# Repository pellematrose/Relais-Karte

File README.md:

# Relais-Karte

Relais-Karte für 24V-Systeme, zum schalten von induktiven Lasten.

---

## 🔧 Gedachte Verwendung

Über **J1** wird die Schaltung mit Strom versorgt.  
Über **J2** kann eine weitere Platine mit Spannung versorgt werden.

Eine **Autosicherung** schützt die Schaltung bzw. die angeschlossene Last.

Der **Schiebeschalter** ermöglicht es, die Last **unabhängig vom Relais** einzuschalten.

---

## 💡 Statusanzeigen (LEDs)

Die Platine verfügt über **zwei LEDs zur Zustandsanzeige**:

- **LED 1 – Versorgung & Sicherung OK**  
  - Leuchtet, wenn **Spannung anliegt** und die **Sicherung in Ordnung** ist

- **LED 2 – Relais aktiv / Last versorgt**  
  - Leuchtet, wenn das **Relais geschaltet hat** oder der **manuelle Schalter** eingeschaltet ist  
  - → Die angeschlossene **Last erhält Spannung**

---

## ⚙️ Relaissteuerung

An **J4** wird das **Schaltsignal** angeschlossen, mit dem das Relais aktiviert wird.  
Hier kann z. B. ein **Schwimmerschalter** als Schließer verwendet werden.  
Wird ein anderes externes Schaltsignal verwendet, muss auf den GND Pfad geachtet werden!

---

## 🔌 Anschluss der Last

Die Last (z. B. eine **Pumpe**) wird an **J3** angeschlossen.

### Betriebsarten:

- **Relais schaltet EIN (NO - Normally Open):**  
  - Last zwischen **NO (+24V)** und **GND** anschließen  
  - → Last ist aktiv, wenn das Relais angezogen ist

- **Relais schaltet AUS (NC - Normally Closed):**  
  - Last zwischen **NC (+24V)** und **GND** anschließen  
  - → Last ist aktiv, wenn das Relais **nicht** angezogen ist

💡 Es können auch **zwei Lasten gleichzeitig angeschlossen** werden:  
- Eine an **NO**
- Eine an **NC**  
→ Es ist dabei **immer nur eine Last aktiv**  
→ Die Last muss **immer** mit **GND** verbunden werden!

### Anschlussplan

---

## 📝 Sonstiges

Das **weiße Feld** auf der Platine ist für Notizen vorgesehen, z. B.:

- Nummerierung
- Bezeichnung der angeschlossenen Last

---

## 📏 Technische Daten

- Versorgungsspannung: 24V (+-20%)
- Laststrom: 4A (Schiebeschalter, Leiterbahnen)
- **PCB Maße:** 38,5 mm × 77 mm

---

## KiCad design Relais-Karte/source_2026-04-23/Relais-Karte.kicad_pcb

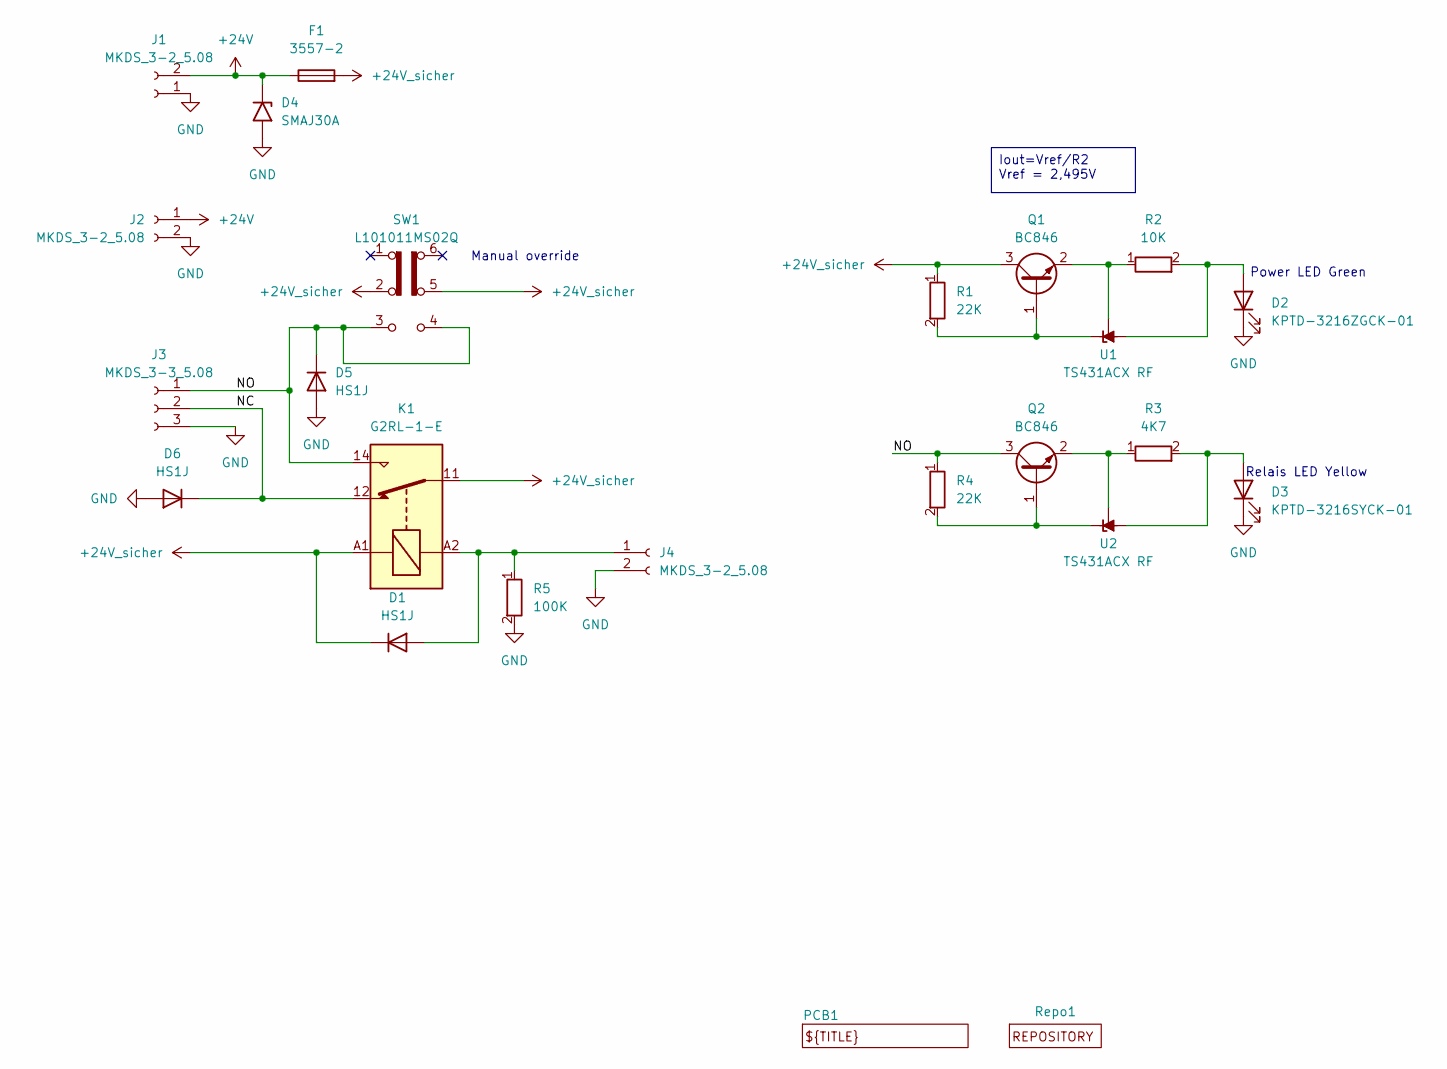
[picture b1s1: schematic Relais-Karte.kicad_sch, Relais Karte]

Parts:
D1, D5, D6: HS1J; D_SMA; Digikey 1801-HS1JCT-ND
D2: KPTD-3216ZGCK-01; LED_1206_3216Metric_ReverseMount_Hole1.8x2.4mm
D3: KPTD-3216SYCK-01; LED_1206_3216Metric_ReverseMount_Hole1.8x2.4mm
D4: SMAJ30A; D_SMA
F1: 3557-2; Fuse Holder Littelfuse ATOF 287; Digikey 36-3557-2-ND
J1, J2, J4: MKDS_3-2_5.08; MKDS_3_2_508; Digikey 277-1027-ND
J3: MKDS_3-3_5.08; MKDS_3_3_508; Digikey 277-1028-ND
K1: G2RL-1-E; Relay_SPDT_Omron_G2RL-1-E; Digikey Z2835-ND
PCB1: _PCB
Q1, Q2: BC846; SOT-23
R1, R4: 22K; R_0603_1608Metric; LCSC C31850
R2: 10K; R_0603_1608Metric; LCSC C25804
R3: 4K7; R_0603_1608Metric; LCSC C23162
R5: 100K; R_0603_1608Metric; LCSC C25803
Repo1: _Repository
SW1: L101011MS02Q; L10101_Schiebeschalter; Digikey CKC5106-ND
U1, U2: TS431ACX RF; SOT-23; Mouser 821-TS431ACXRFG

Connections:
+24V: D4.1 (A1), F1.1, J1.2, J2.1
+24V_sicher: D1.1 (K), F1.2, K1.11, K1.A1, Q1.3 (C), R1.1, SW1.2 (B), SW1.5 (B)
/NC: D6.1 (K), J3.2, K1.12
/NO: D5.1 (K), J3.1, K1.14, Q2.3 (C), R4.1, SW1.3 (C), SW1.4 (A)
GND: D2.1 (K), D3.1 (K), D4.2 (A2), D5.2 (A), D6.2 (A), J1.1, J2.2, J3.3, J4.2, R5.2
unnamed: D1.2 (A), J4.1, K1.A2, R5.1
unnamed: D2.2 (A), R2.2, U1.3 (A)
unnamed: D3.2 (A), R3.2, U2.3 (A)
unnamed: Q1.1 (B), R1.2, U1.2 (K)
unnamed: Q1.2 (E), R2.1, U1.1 (REF)
unnamed: Q2.1 (B), R4.2, U2.2 (K)
unnamed: Q2.2 (E), R3.1, U2.1 (REF)

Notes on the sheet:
Manual override
Relais LED Yellow
Power LED Green
Iout=Vref/R2 Vref = 2,495V

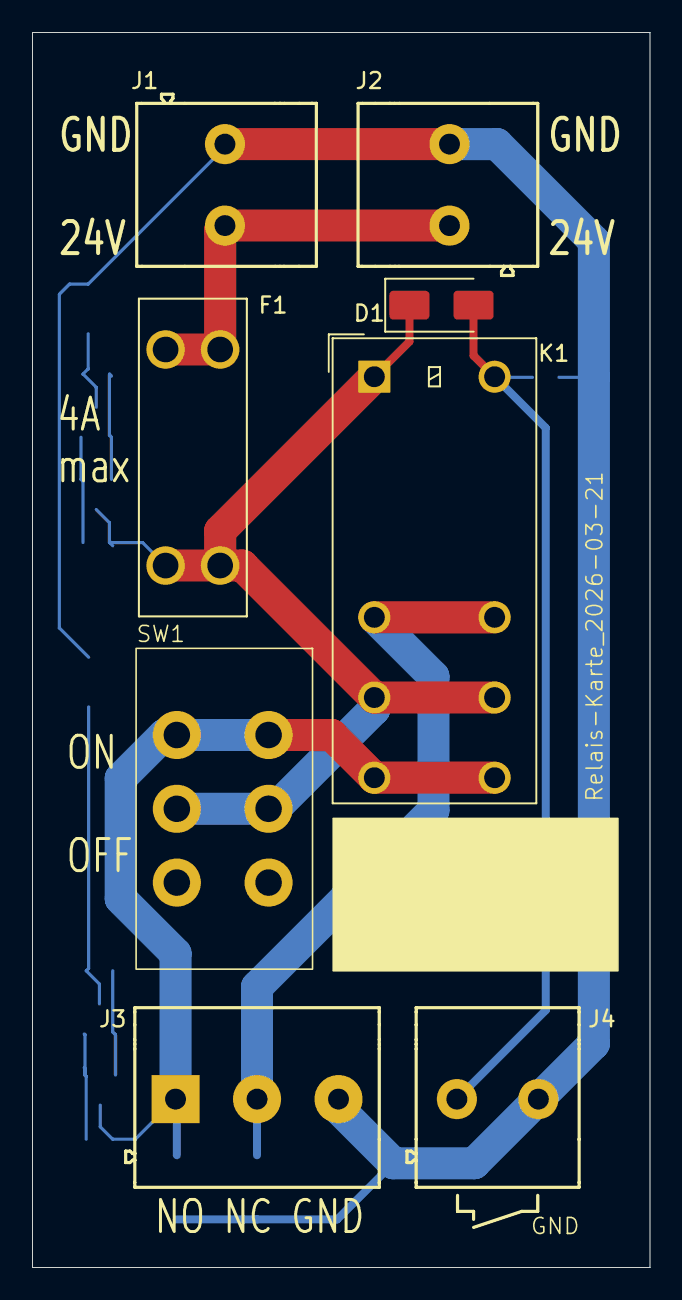
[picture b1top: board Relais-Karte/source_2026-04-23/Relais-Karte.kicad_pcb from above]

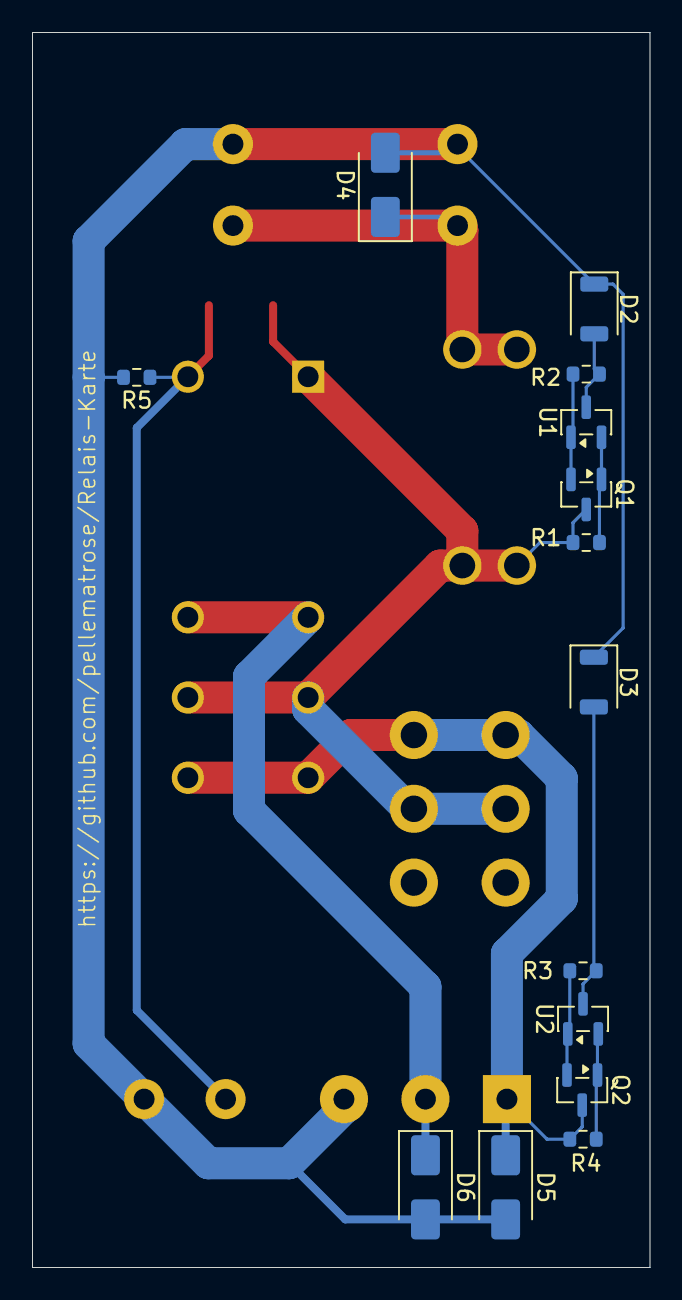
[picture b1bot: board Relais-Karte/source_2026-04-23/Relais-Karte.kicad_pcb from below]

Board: 2 copper layers, 38.5 x 77.0 mm, 24 parts (15 on the bottom side), 12 nets.

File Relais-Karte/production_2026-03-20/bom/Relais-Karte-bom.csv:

"Reference","Value","Footprint","LCSC","Digikey","Mouser"
"D1","HS1J","_PS_LIB_PCB:D_SMA","","1801-HS1JCT-ND",""
"F1","3557-2","_PS_LIB_CON:Fuse Holder Littelfuse ATOF 287","","36-3557-2-ND",""
"J1,J2,J4","MKDS_3-2_5.08","_PS_LIB_CON:MKDS_3_2_508","","277-1027-ND",""
"J3","MKDS_3-3_5.08","_PS_LIB_CON:MKDS_3_3_508","","277-1028-ND",""
"K1","G2RL-1-E","_PS_LIB_PCB:Relay_SPDT_Omron_G2RL-1-E","","Z2835-ND",""
"SW1","L101011MS02Q","_PS_LIB_MECH:L10101_Schiebeschalter","","CKC5106-ND",""

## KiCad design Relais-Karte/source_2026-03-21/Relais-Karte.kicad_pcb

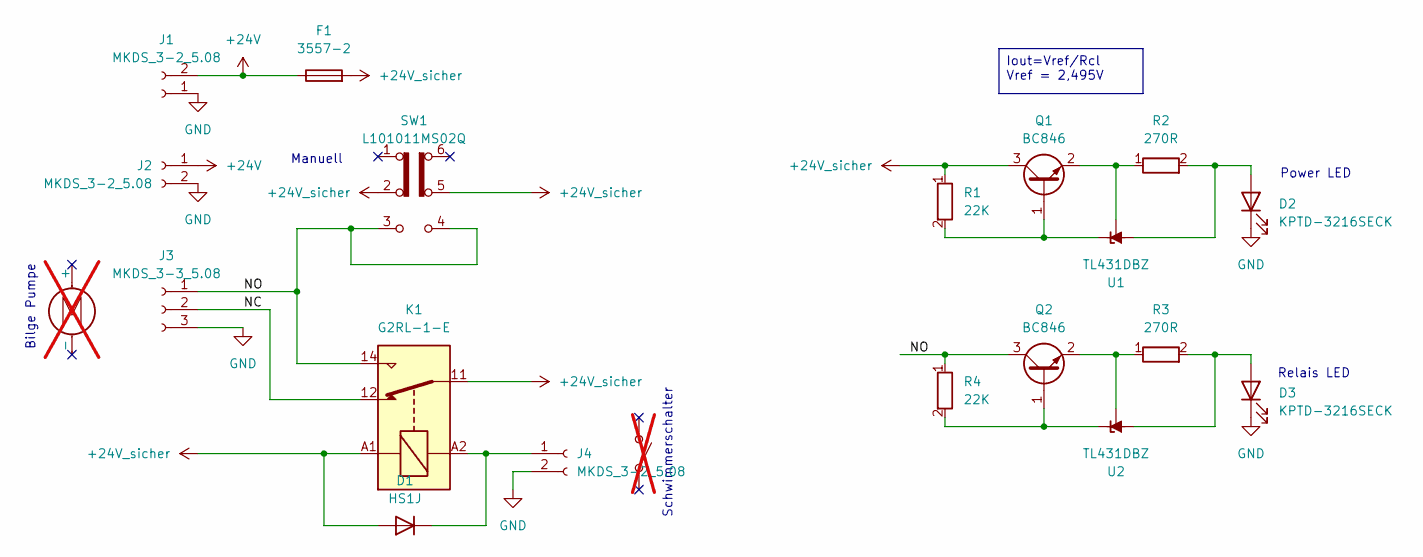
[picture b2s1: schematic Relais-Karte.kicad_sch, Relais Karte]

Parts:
D1: HS1J; D_SMA; Digikey 1801-HS1JCT-ND
D2, D3: KPTD-3216SECK; LED_1206_3216Metric_ReverseMount_Hole1.8x2.4mm
F1: 3557-2; Fuse Holder Littelfuse ATOF 287; Digikey 36-3557-2-ND
J1, J2, J4: MKDS_3-2_5.08; MKDS_3_2_508; Digikey 277-1027-ND
J3: MKDS_3-3_5.08; MKDS_3_3_508; Digikey 277-1028-ND
K1: G2RL-1-E; Relay_SPDT_Omron_G2RL-1-E; Digikey Z2835-ND
M1: Motor_DC; not fitted
Q1, Q2: BC846; SOT-23
R1, R4: 22K; R_0603_1608Metric; LCSC C31850
R2, R3: 270R; R_0603_1608Metric; LCSC C22966
SW1: L101011MS02Q; L10101_Schiebeschalter; Digikey CKC5106-ND
SW2: SW_SPST; not fitted
U1, U2: TL431DBZ; SOT-23

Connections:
+24V: F1.1, J1.2, J2.1
+24V_sicher: D1.2 (A), F1.2, K1.11, K1.A1, Q1.3 (C), R1.1, SW1.2 (B), SW1.5 (B)
/NC: J3.2, K1.12
/NO: J3.1, K1.14, Q2.3 (C), R4.1, SW1.3 (C), SW1.4 (A)
GND: D2.1 (K), D3.1 (K), J1.1, J2.2, J3.3, J4.2
unnamed: D1.1 (K), J4.1, K1.A2
unnamed: D2.2 (A), R2.2, U1.3 (A)
unnamed: D3.2 (A), R3.2, U2.3 (A)
unnamed: Q1.1 (B), R1.2, U1.1 (K)
unnamed: Q1.2 (E), R2.1, U1.2 (REF)
unnamed: Q2.1 (B), R4.2, U2.1 (K)
unnamed: Q2.2 (E), R3.1, U2.2 (REF)

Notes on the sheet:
Bilge Pumpe
Manuell
Relais LED
Schwimmerschalter
Power LED
Iout=Vref/Rcl Vref = 2,495V

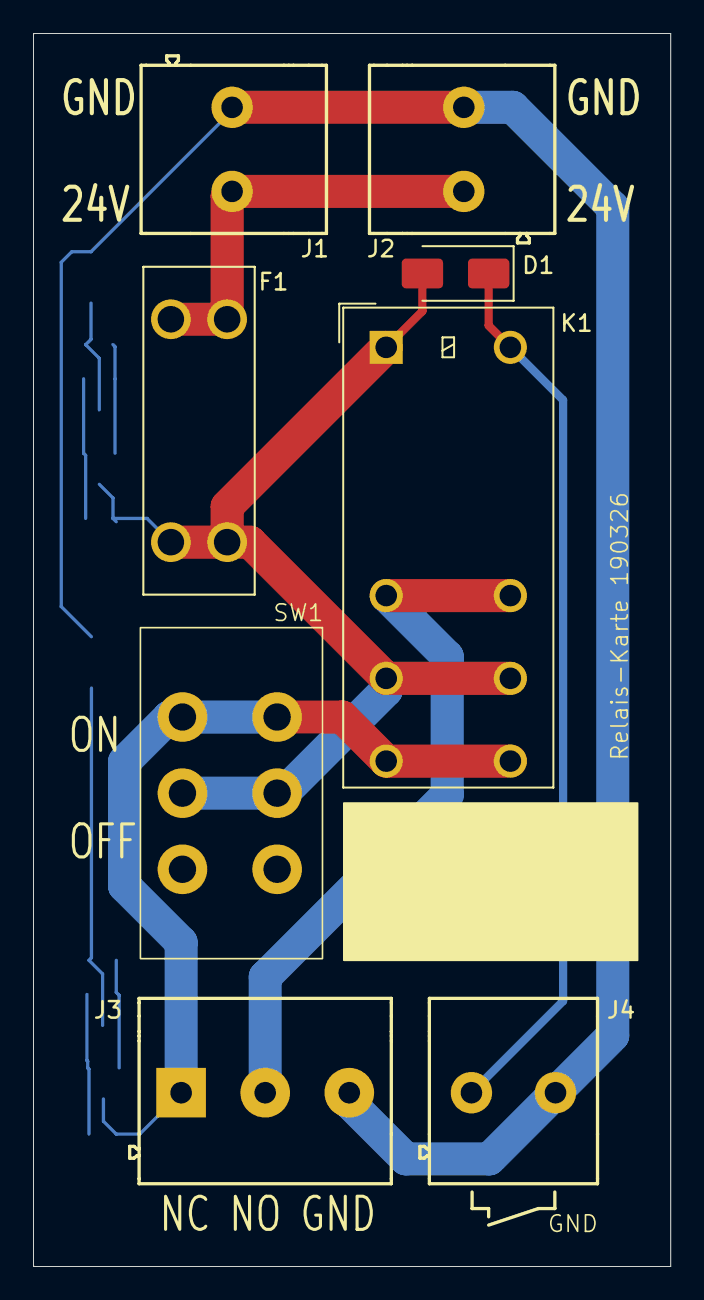
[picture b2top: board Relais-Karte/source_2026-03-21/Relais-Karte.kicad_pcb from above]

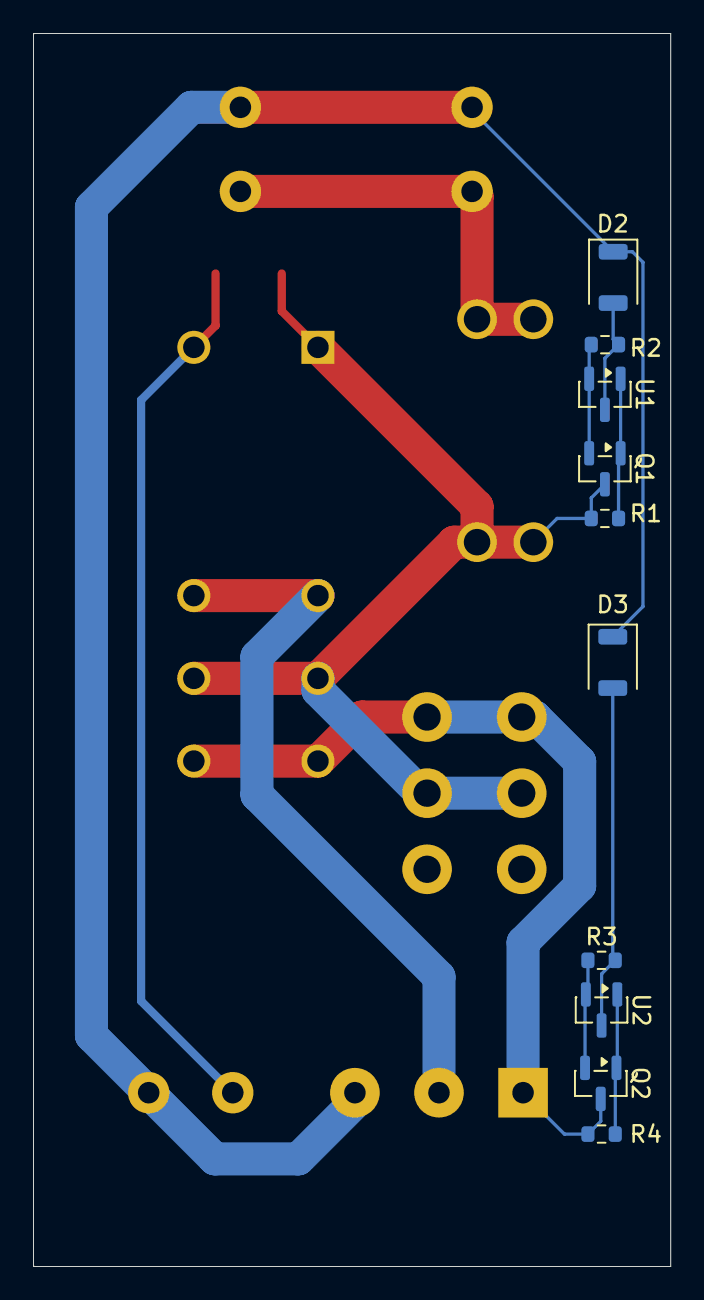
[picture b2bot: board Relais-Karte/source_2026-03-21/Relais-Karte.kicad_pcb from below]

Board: 2 copper layers, 38.5 x 74.5 mm, 18 parts (10 on the bottom side), 12 nets.

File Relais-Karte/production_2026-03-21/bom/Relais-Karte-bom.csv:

"Reference","Value","Footprint","LCSC","Digikey","Mouser"
"D1","HS1J","_PS_LIB_PCB:D_SMA","","1801-HS1JCT-ND",""
"D2,D3","KPTD-3216SECK","_PS_LIB_PCB:LED_1206_3216Metric_ReverseMount_Hole1.8x2.4mm","","",""
"F1","3557-2","_PS_LIB_CON:Fuse Holder Littelfuse ATOF 287","C19727304","36-3557-2-ND",""
"J1,J2,J4","MKDS_3-2_5.08","_PS_LIB_CON:MKDS_3_2_508","C475092","277-1027-ND",""
"J3","MKDS_3-3_5.08","_PS_LIB_CON:MKDS_3_3_508","C475093","277-1028-ND",""
"K1","G2RL-1-E","_PS_LIB_PCB:Relay_SPDT_Omron_G2RL-1-E","","Z2835-ND",""
"Q1,Q2","BC846","Package_TO_SOT_SMD:SOT-23","","",""
"R1,R4","22K","Resistor_SMD:R_0603_1608Metric","C31850","",""
"R2,R3","270R","Resistor_SMD:R_0603_1608Metric","C22966","",""
"SW1","L101011MS02Q","_PS_LIB_MECH:L10101_Schiebeschalter","","CKC5106-ND",""
"U1,U2","TL431DBZ","Package_TO_SOT_SMD:SOT-23","","",""

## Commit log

2026-03-19 v0.1
    erc / drc 0 errors
2026-03-19 add 3d render image
2026-03-21 leds added
2026-03-22 länge der platine angepasst
2026-03-23 added gerber zip file
2026-03-23 led typ angepasst
2026-04-05 final version
2026-04-23 error fixing V1.1
    D1 fixed polarity
    Silk: NC <-> NO
    LED resistors value updated
    U3, U4 -> TS431ACX RF
2026-05-04 anschlussplan hinzugefügt.

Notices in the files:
Relais-Karte.kicad_sch:
CERN-OHL-S v2
(c) 2026 Per-Simon Saal
Relais-Karte/source_2026-03-20/Relais-Karte.kicad_sch:
Licensed under CERN-OHL-S v2
Relais-Karte/source_2026-04-23/Relais-Karte.kicad_pcb:
© 2026 Per-Simon Saal
